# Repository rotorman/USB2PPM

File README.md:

# USB2PPM
Interface to control a remote device (e.g. a drone) from the PC via a radio link.

The USB2PPM circuit gets the signal from PC over USB connection and converts it to Pulse-Position-Modulation (PPM) to be input e.g. over a trainer jack into a remote control transmitter.

USB2PPM outputs standard trainer port signal. You will find Eagle schematic & board files, Microchip MPLAB X PIC32 Harmony project (including pre-built firmware HEX) and two Microsoft Visual Studio .NET C# projects (incl. pre-built Windows binary) to control the board.

USB2PPM circuit connects via USB-port of the PC and communicates over virtual serial port. Where the control input stems, depends only on the software running on the PC that transmits this info to the USB2PPM device.

### Communication protocol

The communication protocol is kept very simple. The connection with USB2PPM is with 115200 baud, 8N1. 

USB2PPM expects a constant 2 byte header (`0xF0 0xC4`) followed by eight uint16 values, sent MSB first (big-endian). Each of these uint16 values corresponds to a servo channel, starting with servo 1.

In the present firmware, the uint16 values code the servo channel pulse width in 200 ns resolution. The minimum accepted value is 1 ms (meaning value 5000 in decimal or `0x1388` in hex) and the maximum accepted value is 2 ms (meaning value 10000 or `0x2710` in hex).  Inputs outside the limits are capped to the borders of these limits (e.g., if you accidentally send 15000, the PIC32 firmware limits this input to 10000).

The USB2PPM echos the accepted input commands in human readable form (ASCII) back. There is no need to read, parse or acknowledge this feedback.

When sending the servo control telegram, you also do not need to adhere to any timing constraints or intervals when sending the data - after the telegram with new values has been accepted by USB2PPM, it continues to send out servo pulses with the commanded data until a new telegram with updated values is sent to it.

#### Examples

1) all 8 channels centered (1.5 ms)

`0xF0 0xC4  0x1D 0x4C 0x1D 0x4C 0x1D 0x4C 0x1D 0x4C 0x1D 0x4C 0x1D 0x4C 0x1D 0x4C 0x1D 0x4C`

2) all 8 channels minimum (1 ms):

`0xF0 0xC4 0x13 0x88 0x13 0x88 0x13 0x88 0x13 0x88 0x13 0x88 0x13 0x88 0x13 0x88 0x13 0x88`

3) all 8 channels maximum (2 ms):

`0xF0 0xC4 0x27 0x10 0x27 0x10 0x27 0x10 0x27 0x10 0x27 0x10 0x27 0x10 0x27 0x10 0x27 0x10`

4) channel 7 at 1.7 ms, rest at center:

`0xF0 0xC4  0x1D 0x4C 0x1D 0x4C 0x1D 0x4C 0x1D 0x4C 0x1D 0x4C 0x1D 0x4C 0x21 0x34 0x1D 0x4C`

(1.7 ms in 200 ns steps is 8500 that is in hex '0x2134'. The value 8500 stems from equation:

`pulse_width / step_size`

and here with example values for 1.7ms pulse width: 1.7 * 1000 * 1000 / 200 = 8500.

The first 1000 in the multiplication is to get from milliseconds to microseconds and the second multiplication with 1000 to get from microsecons to nanoseconds.

### Discussion

Project discussion in RC Groups forum blog post:

<https://www.rcgroups.com/forums/showthread.php?3845229-Blog-10-USB2PPM-Interface-for-controlling-a-remote-device-from-PC>

# S.BUS

The subfolder FTDI_SBUS has some examples of how to directly output a S.BUS signal from a computer, using e.g. a [FTDI adapter](https://www.sparkfun.com/products/9717) and an [inverter](https://oshwlab.com/feather/S_Bus_Inverter_R2-fWQK2kewO). The inverter can be skipped, if the receiving end expects inverted S.BUS (=non-inverted UART) signal anyhow, for example [RadioMaster TX16S](https://www.radiomasterrc.com/products/tx16s-mark-ii-radio-controller) AUX-ports, used as S.BUS trainer inputs.

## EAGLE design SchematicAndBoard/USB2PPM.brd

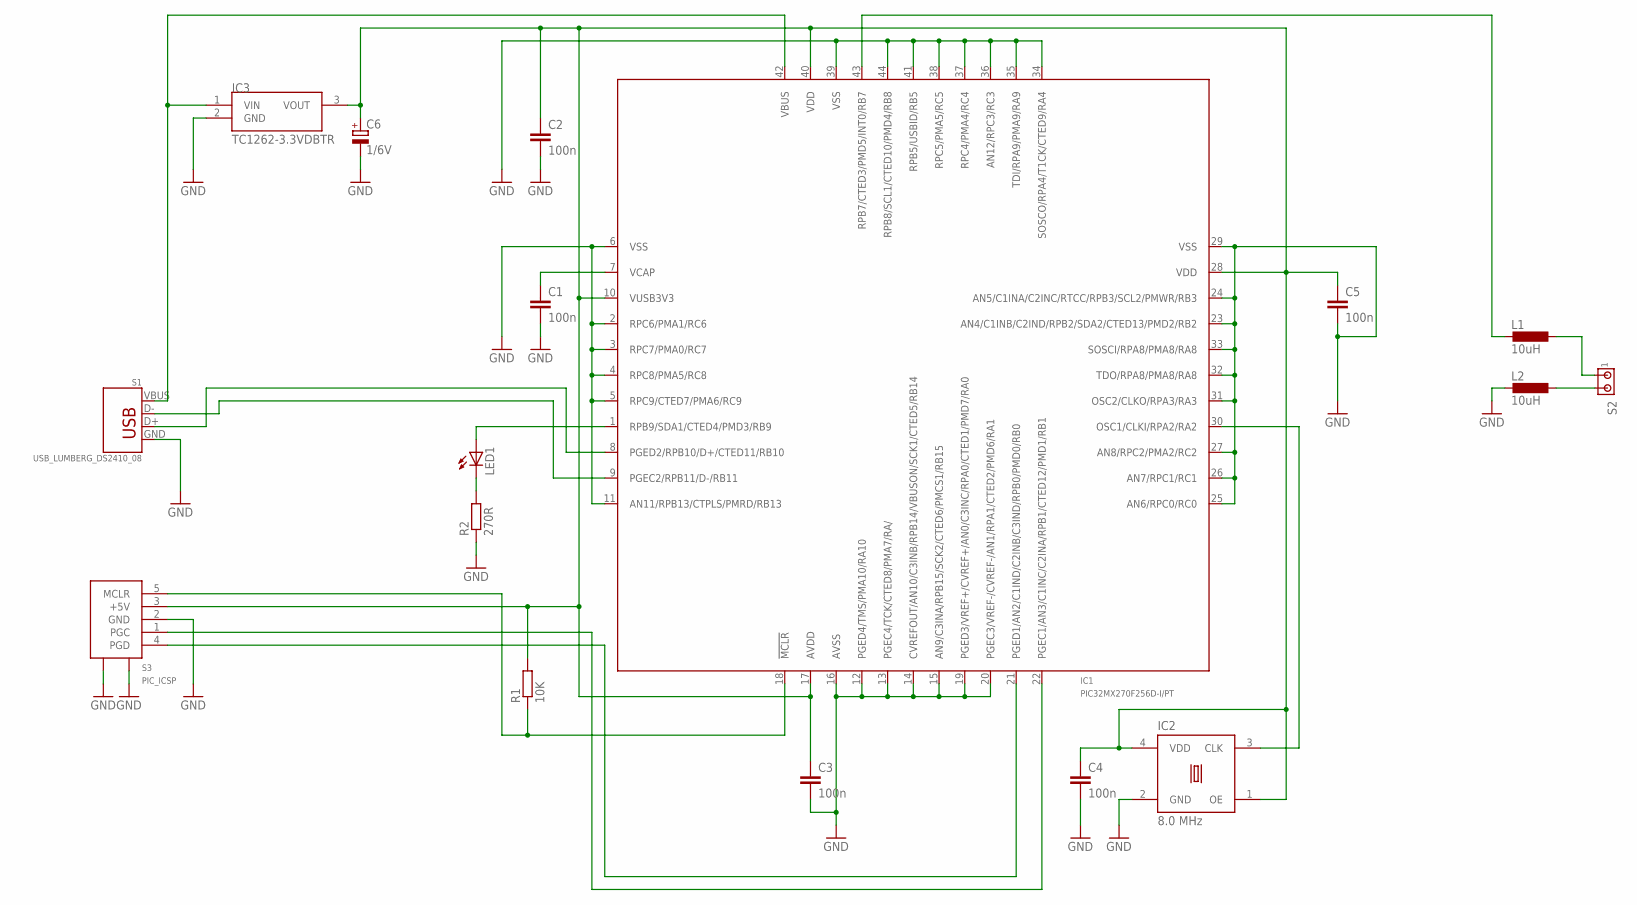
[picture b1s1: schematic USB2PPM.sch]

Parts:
C1, C2, C3, C4, C5: 100n; C0805K
C6: 1/6V; SMC_A
IC1: PIC32MX270F256D-I/PT; TQFP44
IC2: 8.0 MHz; DFN_3.2X5MM(4MM)
IC3: TC1262-3.3VDBTR; SOT223
L1, L2: 10uH; L3225M
LED1: LEDSML0805; SML0805
R1: 10K; R0805W
R2: 270R; R0805W
S1: USB_LUMBERG_DS2410_08; USB-A-LUMBERG_DS2410_08
S2: MTA02-100; 10X02MTA
S3: PIC_ICSP; 53395-05_GND

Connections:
!MCLR: IC1.18 (!MCLR), R1.1, S3.5 (MCLR)
+5V_USB: IC1.42 (VBUS), IC3.1 (VIN), S1.VBUS (GND)
D+: IC1.8 (PGED2/RPB10/D+/CTED11/RB10), S1.D+ (D-)
D-: IC1.9 (PGEC2/RPB11/D-/RB11), S1.D- (D+)
GND: C1.2, C2.2, C3.2, C4.2, C5.2, C6.-, IC1.2 (RPC6/PMA1/RC6), IC1.3 (RPC7/PMA0/RC7), IC1.4 (RPC8/PMA5/RC8), IC1.5 (RPC9/CTED7/PMA6/RC9), IC1.6 (VSS), IC1.11 (AN11/RPB13/CTPLS/PMRD/RB13), IC1.12 (PGED4/TMS/PMA10/RA10), IC1.13 (PGEC4/TCK/CTED8/PMA7/RA/), IC1.14 (CVREFOUT/AN10/C3INB/RPB14/VBUSON/SCK1/C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), IC1.15 (AN9/C3INA/RPB15/SCK2/CTED6/PMCS1/RB15), IC1.16 (AVSS), IC1.19 (PGED3/VREF+/CVREF+/AN0/C3INC/RPA0/CTED1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), IC1.20 (PGEC3/VREF-/CVREF-/AN1/RPA1/CTED2/PMD6/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), IC1.23 (AN4/C1INB/C2IND/RPB2/SDA2/CTED13/PMD2/R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), IC1.24 (AN5/C1INA/C2INC/RTCC/RPB3/SCL2/PMWR/RB3), IC1.25 (AN6/RPC0/RC0), IC1.26 (AN7/RPC1/RC1), IC1.27 (AN8/RPC2/PMA2/RC2), IC1.29 (VSS), IC1.31 (OSC2/CLKO/RPA3/RA3), IC1.32 (TDO/RPA8/PMA8/RA8), IC1.33 (SOSCI/RPA8/PMA8/RA8), IC1.34 (SOSCO/RPA4/T1CK/CTED9/RA4), IC1.35 (TDI/RPA9/PMA9/RA9), IC1.36 (AN12/RPC3/RC3), IC1.37 (RPC4/PMA4/RC4), IC1.38 (RPC5/PMA5/RC5), IC1.39 (VSS), IC1.41 (RPB5/USBID/RB5), IC1.44 (RPB8/SCL1/CTED10/PMD4/RB8), IC2.2 (GND), IC3.2 (GND), L2.2, R2.1, S1.GND (VBUS), S3.2 (GND), S3.S1 (GND), S3.S2 (GND)
LED: IC1.1 (RPB9/SDA1/CTED4/PMD3/RB9), LED1.A
unnamed: LED1.C, R2.2
OSC: IC1.30 (OSC1/CLKI/RPA2/RA2), IC2.3 (CLK)
PGC: IC1.22 (PGEC1/AN3/C1INC/C2INA/RPB1/CTED12/PMD1/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), S3.1 (PGC)
PGD: IC1.21 (PGED1/AN2/C1IND/C2INB/C3IND/RPB0/PMD0/R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), S3.4 (PGD)
PPM: IC1.43 (RPB7/CTED3/PMD5/INT0/RB7), L1.2
PPM_GND: L2.1, S2.2
PPM_OUT: L1.1, S2.1
VCAP: C1.1, IC1.7 (VCAP)
VDD: C2.1, C3.1, C4.1, C5.1, C6.+, IC1.10 (VUSB3V3), IC1.17 (AVDD), IC1.28 (VDD), IC1.40 (VDD), IC2.1 (OE), IC2.4 (VDD), IC3.3 (VOUT), R1.2, S3.3 (+5V)

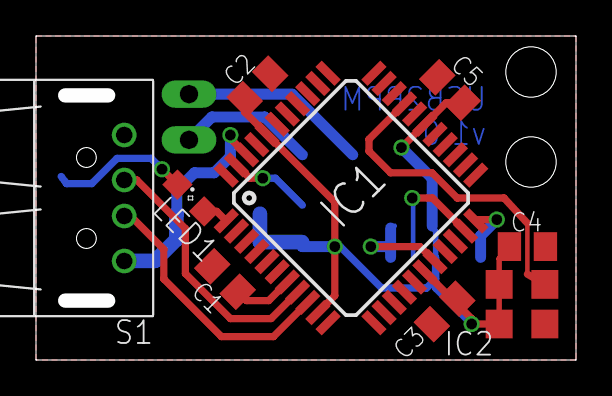
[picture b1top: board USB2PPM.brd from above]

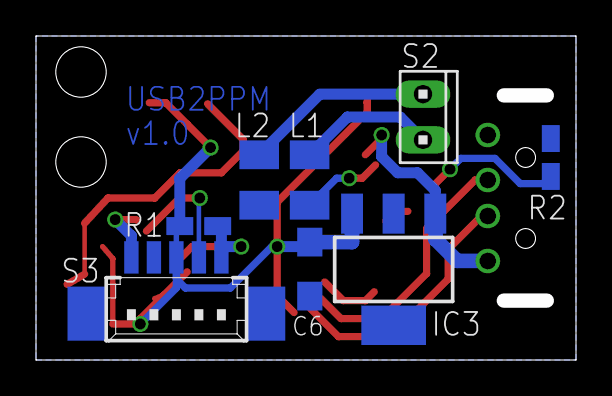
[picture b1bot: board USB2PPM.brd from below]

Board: 2 copper layers, 29.2 x 17.2 mm, 17 parts (8 on the bottom side), 15 nets.

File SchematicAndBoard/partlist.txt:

C1-C5  100nF                 SMD 0805
C6     1µF 6V                SMC-A
IC1    PIC32MX270F256D-I/PT  TQFP44
IC2    8.0 MHz 3.3V Osc      DFN_3.2X5MM  EuroQuarz 8.000MHZ XO53050UITA
IC3    TC1262-3.3VDBTR       SOT223
L1-L2  10µH                  SMD 3225
LED1   green                 SMD 0805
R1     10K                   SMD 0805
R2     270R                  SMD 0805
S1     USB-A                 LUMBERG 53842
S2     3,5mm mono jack with cable
S3     ICSP header, Molex PicoBlade 53398-0571

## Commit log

2021-03-07 Update README.md
    Added project description
2021-03-07 Initial state
2021-03-07 Update README.md
    Added images
2021-03-07 Update README.md
    Images side-by-side
2021-03-07 Update README.md
    Project discussion link
2021-03-29 Added a joystick demo.
2021-03-29 Added SlimDX.Dll also here for easier access.
2021-03-29 Update README.md
    Two examples
2022-12-03 Added steering wheel demo
2022-12-03 Updated a comment.
2022-12-03 Added the binary for easier download. Works with FTDI adapter, connected e.g. to a RadioMaster TX16S, configured as AUX1 or AUX2 SBUS trainer.
2022-12-03 Moved to FTDI_SBUS subfolder. Added ch4 and ch5 as mixed throttle and brake channels, where ch5 is brake priority mode mix.
2022-12-03 clean code
2022-12-05 Added basic S.BUS out FTDI demo.
2022-12-05 Added description about S.BUS
2022-12-06 deleted the exe
